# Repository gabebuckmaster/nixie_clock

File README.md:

# Nixie Tube Clock

A minimalist nixie tube clock design in a cnc-machined hardwood case using IN12B tubes.

All of the design files and detailed assembly/compilation instructions for the electronics, mechanical components, and firmware can be found in the respective subfolders: <a href=electronics>Electronics</a>, <a href=mechanical>Mechanical</a>, and <a href=firmware>Firmware</a>. 

This design has gone through several iterations, mostly to simplify the design and remove extraneous features that I thought would be a good idea but ultimately weren't. While nixie tubes are beautiful, they objectively have some significant shortcomings as a display technology: their viewing angle is extremely limited, and they can't be dimmed to arbitrarily low brightnesses - not to mention the difficulty in working with the high voltages needed to drive them. Over the course of the project, the goal converged to showing off the beauty of nixie tubes with the minimum possible set of features, and I'm happy with how the final result aligns with this goal.

I learned a lot about cnc machining, and am left with a great respect for the people who do this for a living. An incredible amount of effort (and skill among those who practice this professionally) goes into simply clamping the work piece in a way that allows the router/mill the necessary access. I also learned a lot about boost converter design, specifically core losses, the huge range of magnetic core materials, and why power electronics people often advise against designing boost converters that operate in DCM.

## License and Disclaimer
I built this clock because I wanted it to exist, and I’m distributing the documentation in the hopes that others find it interesting and/or educational. To this end, the files provided in this repository are licensed under the MIT license unless otherwise noted a given file.

This design is not FCC, CE, or UL certified, and thus it is probably not legal nor advisable to sell this design as a finished product in your jurisdiction. This project involves potentially dangerous power tools, potentially lethal voltages, and potential fire hazard due to housing electronics in a flammable material. **If you choose to recreate any work documented in this repository, you do so entirely at your own risk.**

## Final Assembly
The bill of materials for the final assembly is in <a href="final_assembly_bom.csv">Final Assembly BOM</a>.

### Pseudo-exploded view of the final assembly

### Video of final assembly
<p align="center">

</p>
Click through for longer/higher resolution video of final assembly.

## More Photos
### Final Assembly

### Electronics

### Clock Body

### Back Panel

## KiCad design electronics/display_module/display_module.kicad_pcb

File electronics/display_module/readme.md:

# Display Module

This PCB includes the nixie tubes themselves, current limiting resistors, and the high voltage shift register. 

For assembly, see the  <a href="display_module_bom.csv">BOM</a> and <a href="gerbers/display_module-F_Fab.pdf">fab drawing</a>

<a href="control_module.pdf">Schematic PDF</a>

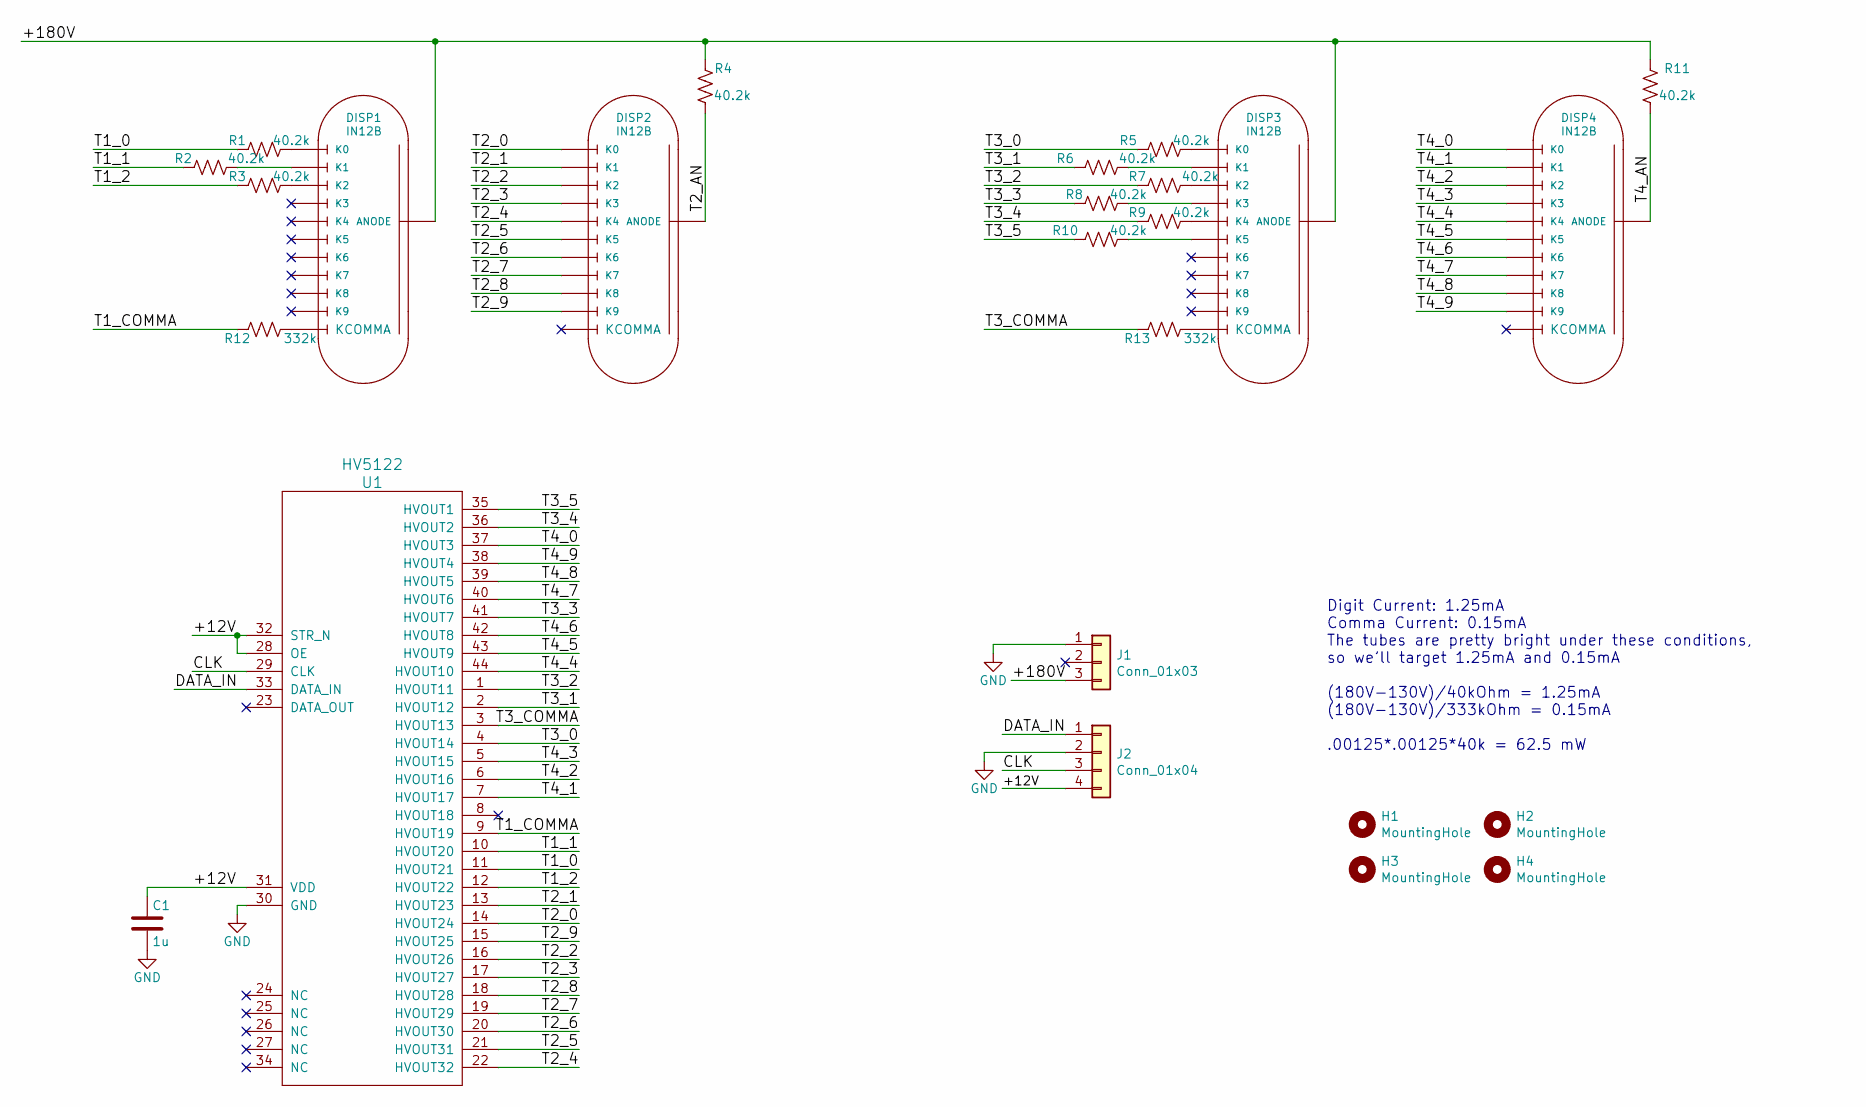
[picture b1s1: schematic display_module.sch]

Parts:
C1: 1u; C_0805_2012Metric
DISP1, DISP2, DISP3, DISP4: IN12B; IN-12B_nosocket
H1, H2, H3, H4: MountingHole; MountingHole_2.2mm_M2
J1: Conn_01x03; PinHeader_1x03_P2.54mm_Vertical
J2: Conn_01x04; PinHeader_1x04_P2.54mm_Vertical
R1, R2, R3, R4, R5, R6, R7, R8, R9, R10, R11: 40.2k; R_0805_2012Metric
R12, R13: 332k; R_0805_2012Metric
U1: HV5122; PQFP-44_10x10mm_Pitch0.8mm

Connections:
/+12V: C1.1, J2.4, U1.28 (OE), U1.31 (VDD), U1.32 (STR_N)
/+180V: DISP1.1 (ANODE), DISP3.1 (ANODE), J1.3, R4.1, R11.1
/CLK: J2.3, U1.29 (CLK)
/DATA_IN: J2.1, U1.33 (DATA_IN)
/T1_0: R1.2, U1.11 (HVOUT21)
/T1_1: R2.2, U1.10 (HVOUT20)
/T1_2: R3.2, U1.12 (HVOUT22)
/T1_COMMA: R12.2, U1.9 (HVOUT19)
/T2_0: DISP2.2 (K0), U1.14 (HVOUT24)
/T2_1: DISP2.11 (K1), U1.13 (HVOUT23)
/T2_2: DISP2.10 (K2), U1.16 (HVOUT26)
/T2_3: DISP2.9 (K3), U1.17 (HVOUT27)
/T2_4: DISP2.8 (K4), U1.22 (HVOUT32)
/T2_5: DISP2.7 (K5), U1.21 (HVOUT31)
/T2_6: DISP2.6 (K6), U1.20 (HVOUT30)
/T2_7: DISP2.5 (K7), U1.19 (HVOUT29)
/T2_8: DISP2.4 (K8), U1.18 (HVOUT28)
/T2_9: DISP2.3 (K9), U1.15 (HVOUT25)
/T2_AN: DISP2.1 (ANODE), R4.2
/T3_0: R5.2, U1.4 (HVOUT14)
/T3_1: R6.2, U1.2 (HVOUT12)
/T3_2: R7.2, U1.1 (HVOUT11)
/T3_3: R8.2, U1.41 (HVOUT7)
/T3_4: R9.2, U1.36 (HVOUT2)
/T3_5: R10.2, U1.35 (HVOUT1)
/T3_COMMA: R13.2, U1.3 (HVOUT13)
/T4_0: DISP4.2 (K0), U1.37 (HVOUT3)
/T4_1: DISP4.11 (K1), U1.7 (HVOUT17)
/T4_2: DISP4.10 (K2), U1.6 (HVOUT16)
/T4_3: DISP4.9 (K3), U1.5 (HVOUT15)
/T4_4: DISP4.8 (K4), U1.44 (HVOUT10)
/T4_5: DISP4.7 (K5), U1.43 (HVOUT9)
/T4_6: DISP4.6 (K6), U1.42 (HVOUT8)
/T4_7: DISP4.5 (K7), U1.40 (HVOUT6)
/T4_8: DISP4.4 (K8), U1.39 (HVOUT5)
/T4_9: DISP4.3 (K9), U1.38 (HVOUT4)
/T4_AN: DISP4.1 (ANODE), R11.2
GND: C1.2, J1.1, J2.2, U1.30 (GND)
unnamed: DISP1.2 (K0), R1.1
unnamed: DISP1.10 (K2), R3.1
unnamed: DISP1.11 (K1), R2.1
unnamed: DISP1.12 (KCOMMA), R12.1
unnamed: DISP3.2 (K0), R5.1
unnamed: DISP3.7 (K5), R10.1
unnamed: DISP3.8 (K4), R9.1
unnamed: DISP3.9 (K3), R8.1
unnamed: DISP3.10 (K2), R7.1
unnamed: DISP3.11 (K1), R6.1
unnamed: DISP3.12 (KCOMMA), R13.1

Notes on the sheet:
Digit Current: 1.25mA Comma Current: 0.15mA The tubes are pretty bright under these conditions, so we’ll target 1.25mA and 0.15mA (180V-130V)/40kOhm = 1.25mA (180V-130V)/333kOhm = 0.15mA .00125*.00125*40k = 62.5 mW

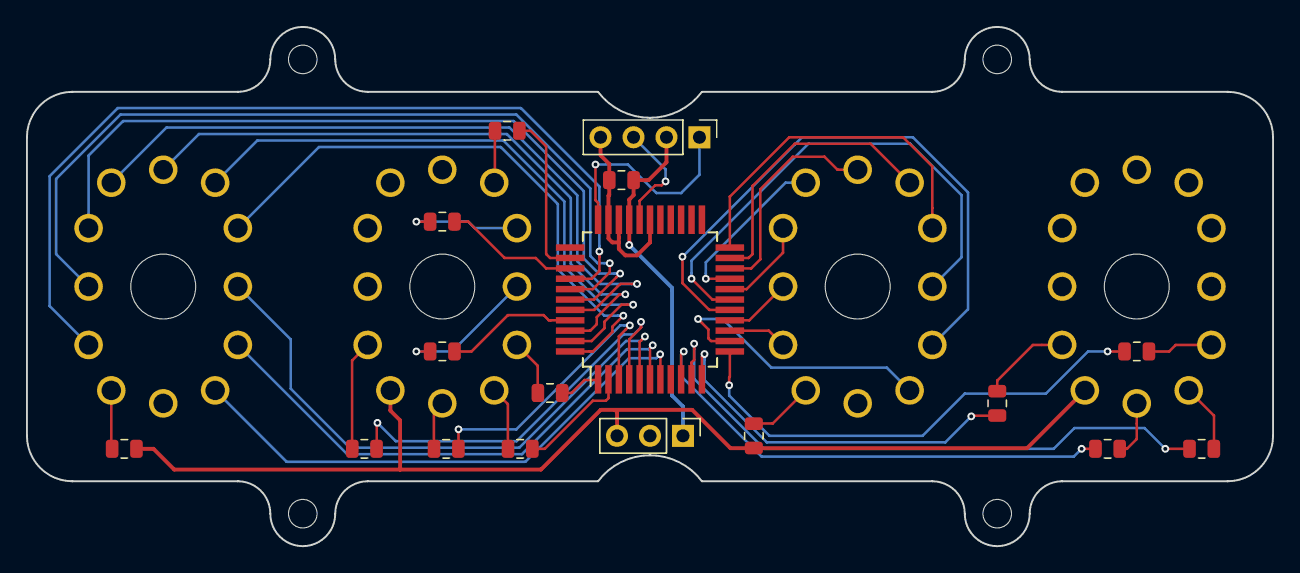
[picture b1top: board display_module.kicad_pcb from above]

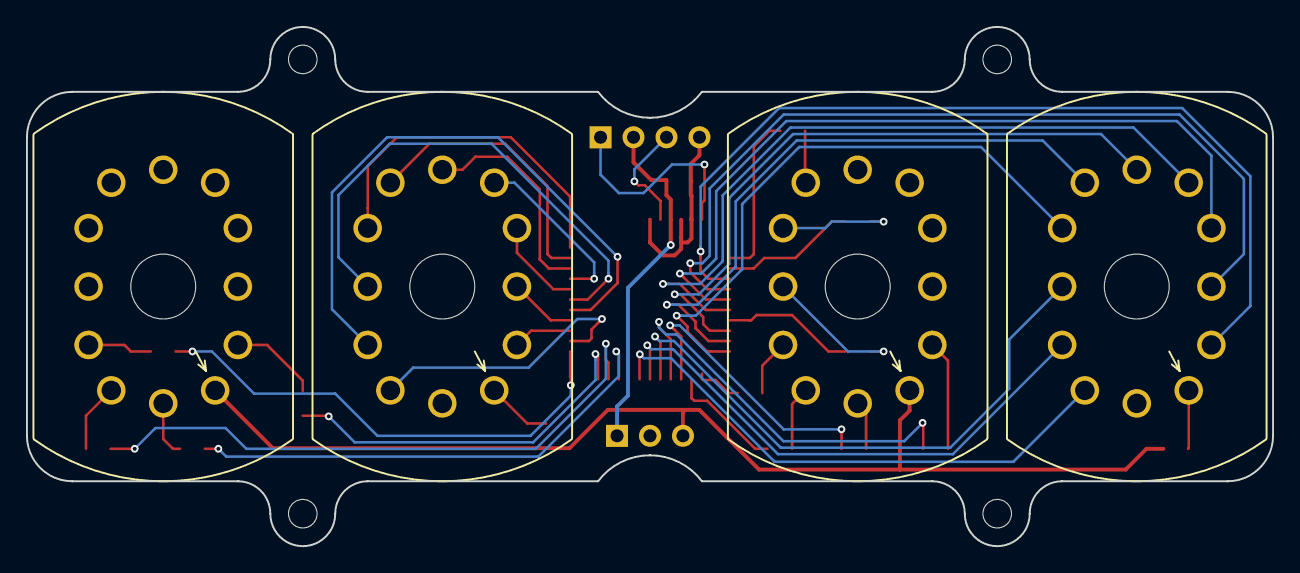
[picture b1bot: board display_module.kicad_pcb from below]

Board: 2 copper layers, 96.0 x 40.0 mm, 25 parts (4 on the bottom side), 49 nets.

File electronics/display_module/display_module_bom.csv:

Reference(s),Qty,Description,Value,Manufacturer,MPN
C1,1,1 uF Ceramic Capacitor X5R 25V 0805,1u,Generic,
"DISP1, DISP2, DISP3, DISP4",4,IN12B Nixie Tube,,,
J1,1,"0.1"" Male Pin Header 1x3 TH",,Generic,
J2,1,"0.1"" Male Pin Header 1x4 TH",,Generic,
"R1, R2, R3, R4, R5, R6, R7, R8, R9, R10, R11",11,1% Resistor 0805,40.2k,,
"R12, R13",2,1% Resistor 0805,332k,,
U1,1,High Voltage Shift Register,,Microchip,HV5122

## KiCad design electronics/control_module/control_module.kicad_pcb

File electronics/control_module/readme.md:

# Control Module

This PCB includes the microcontroller, a temperature compensated real time clock IC with battery backup, and the boost converter that generates the 180V supply for the nixie tubes.

For assembly, see the  <a href="control_module_bom.csv">BOM</a> and <a href="gerbers/control_module-F_Fab.pdf">fab drawing</a>

<a href="control_module.pdf">Schematic PDF</a>

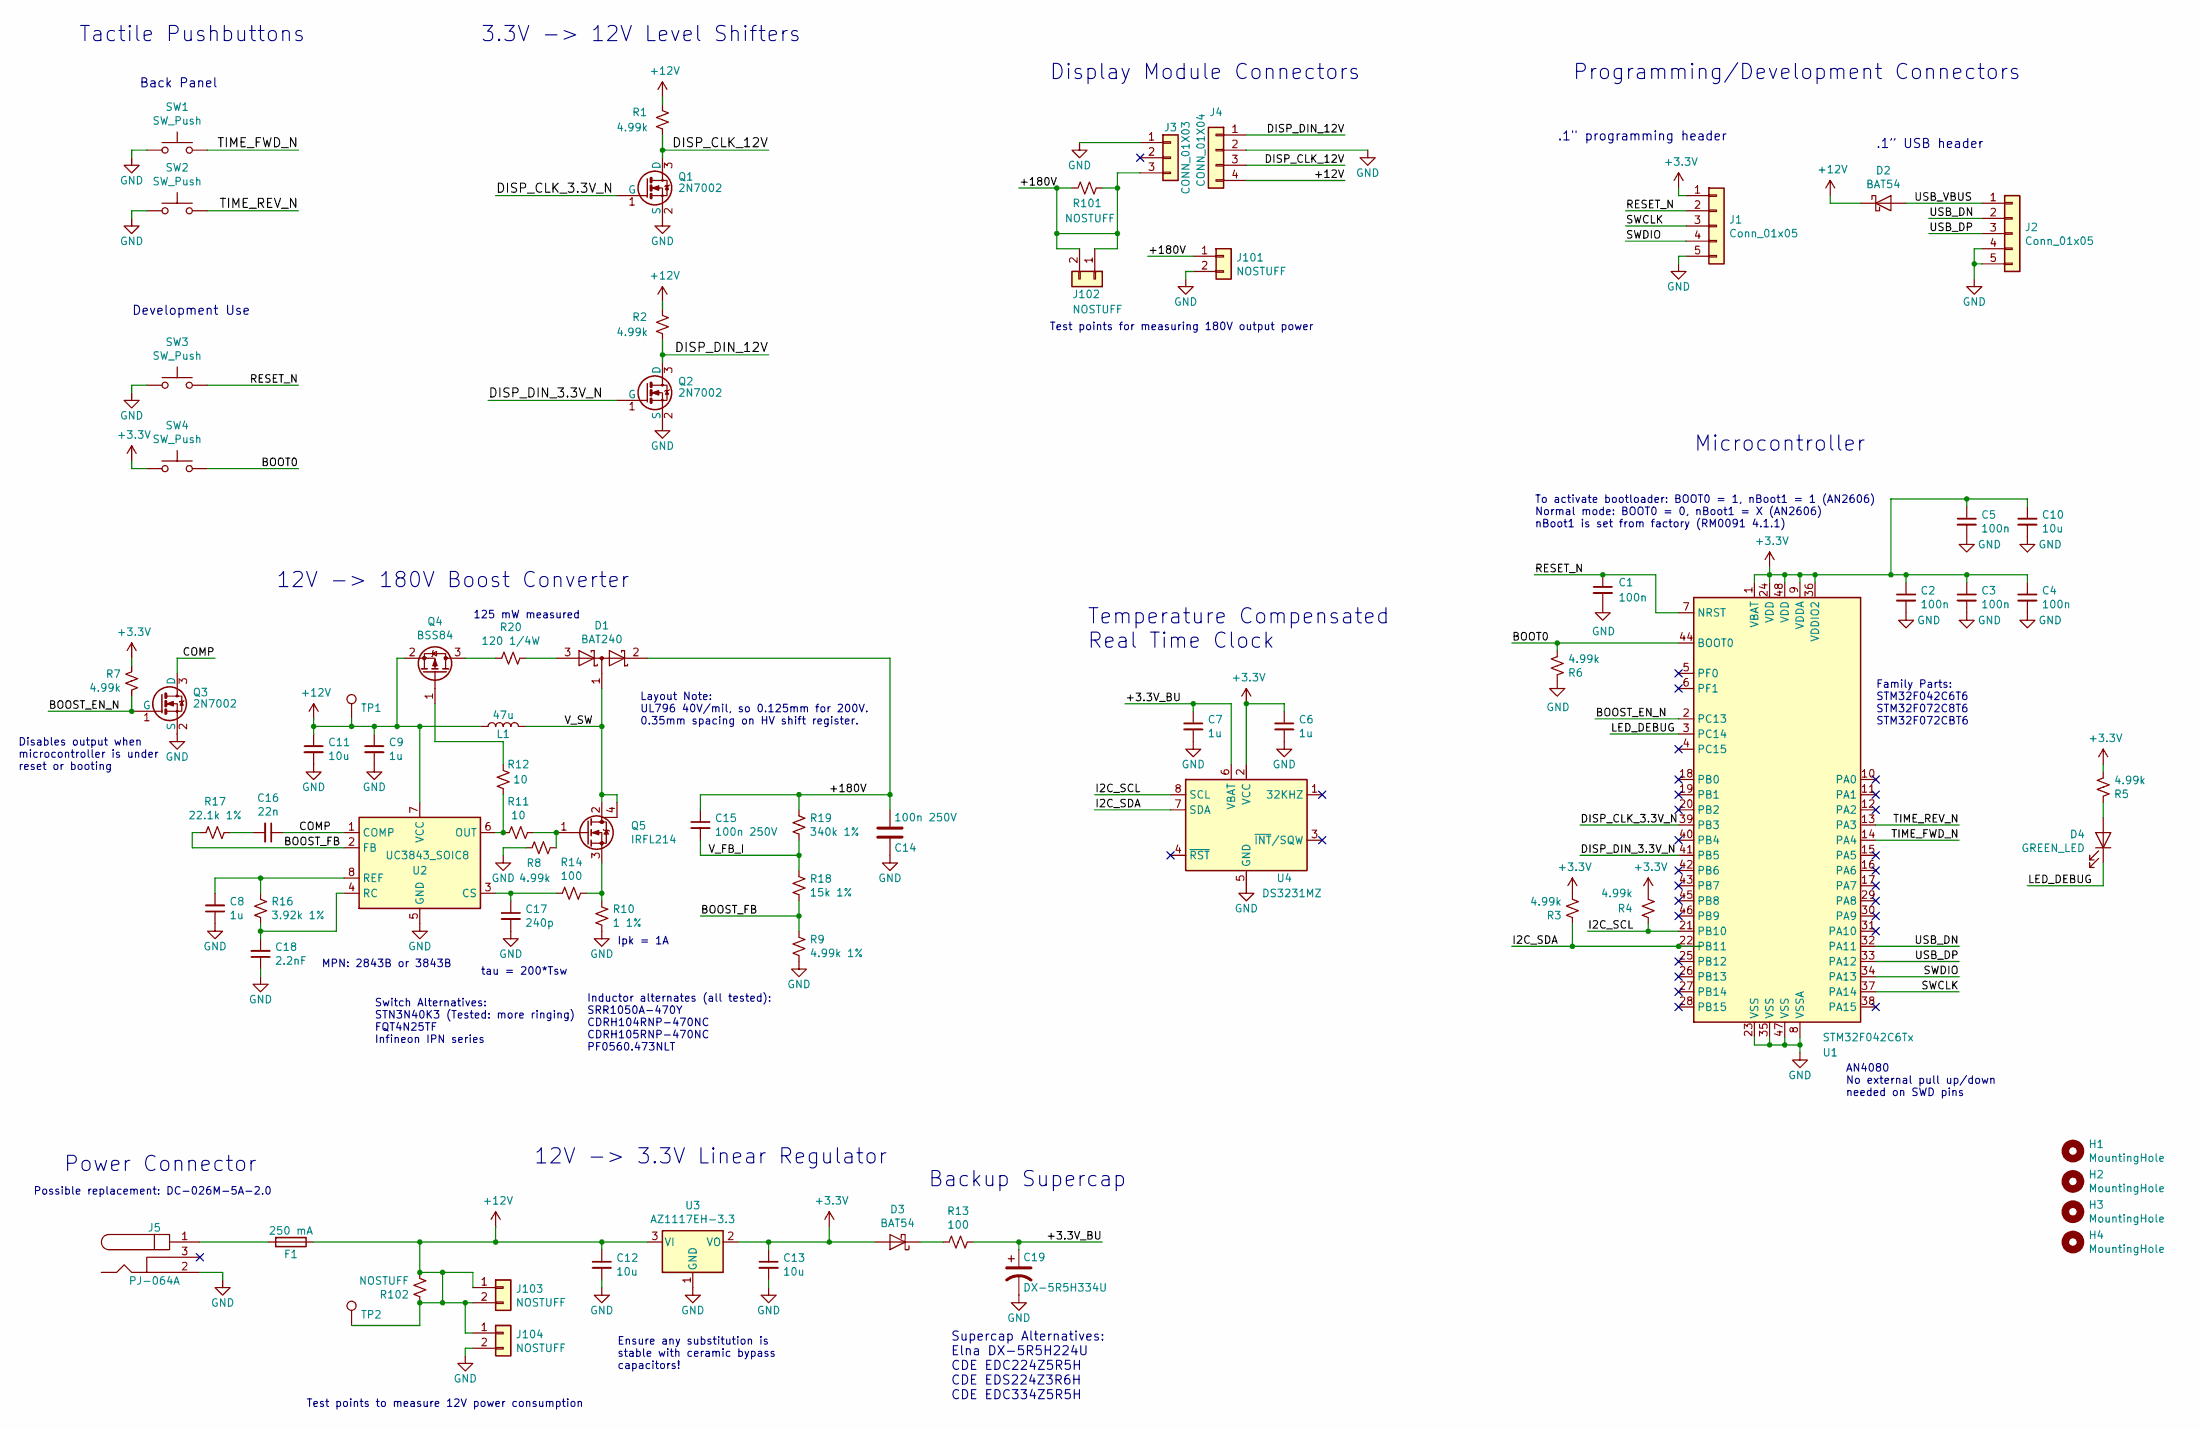
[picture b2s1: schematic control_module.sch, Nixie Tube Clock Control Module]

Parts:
C1, C2, C3, C4, C5: 100n; C_0805_2012Metric
C6, C7, C8, C9: 1u; C_0805_2012Metric
C10, C11, C12, C13: 10u; C_0805_2012Metric
C14, C15: 100n 250V; C_1206_3216Metric
C16: 22n; C_0805_2012Metric
C17: 240p; C_0805_2012Metric
C18: 2.2nF; C_0805_2012Metric
C19: DX-5R5H334U; EEC-S0HD334H
D1: BAT240; SOT-23
D2, D3: BAT54; D_SOD-123
D4: GREEN_LED; LED_0805_2012Metric
F1: 250 mA; Fuse_1206_3216Metric_Pad1.42x1.75mm_HandSolder
H1, H2, H3, H4: MountingHole; MountingHole_2.2mm_M2
J1, J2: Conn_01x05; PinHeader_1x05_P2.54mm_Vertical_NoSilk
J3: CONN_01X03; PinHeader_1x03_P2.54mm_Vertical
J4: CONN_01X04; PinHeader_1x04_P2.54mm_Vertical
J5: PJ-064A; PJ-064X
J101, J102, J103, J104: NOSTUFF; PinHeader_1x02_P2.54mm_Vertical
L1: 47u; L_TDK_SLF10145; Part Number 74404064221
Q1, Q2, Q3: 2N7002; SOT-23
Q4: BSS84; SOT-23
Q5: IRFL214; SOT-223
R1, R2, R3, R4, R5, R6, R7, R8: 4.99k; R_0805_2012Metric
R9: 4.99k 1%; R_0805_2012Metric
R10: 1 1%; R_0805_2012Metric
R11, R12: 10; R_0805_2012Metric
R13, R14: 100; R_0805_2012Metric
R16: 3.92k 1%; R_0805_2012Metric
R17: 22.1k 1%; R_0805_2012Metric
R18: 15k 1%; R_1206_3216Metric
R19: 340k 1%; R_1206_3216Metric
R20: 120 1/4W; R_1206_3216Metric
R101, R102: NOSTUFF; R_0805_2012Metric
SW1, SW2: SW_Push; SW_PUSH_6mm_H4.3mm
SW3, SW4: SW_Push; SW_SPST_TL3342
TP1, TP2: TestPoint; TestPoint_Pad_D1.0mm
U1: STM32F042C6Tx; LQFP-48_7x7mm_P0.5mm
U2: UC3843_SOIC8; SOIC-8_3.9x4.9mm_P1.27mm
U3: AZ1117EH-3.3; SOT-223-3_TabPin2
U4: DS3231MZ; SOIC-8_3.9x4.9mm_P1.27mm

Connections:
+3V3: C2.1, C3.1, C4.1, C5.1, C6.1, C10.1, C13.1, D3.2 (A), J1.1, R3.2, R4.2, R5.2, R7.1, SW4.1, U1.1 (VBAT), U1.9 (VDDA), U1.24 (VDD), U1.36 (VDDIO2), U1.48 (VDD), U3.2 (VO), U4.2 (VCC)
+12V: C9.1, C11.1, C12.1, D2.1 (K), F1.1, J4.4, J103.1, J103.2, J104.1, L1.1, Q4.2 (S), R1.2, R2.2, R102.1, R102.2, TP1.1, TP2.1, U2.7 (VCC), U3.3 (VI)
/+3.3V_BU: C7.1, C19.1, R13.1, U4.6 (VBAT)
/+180V: C14.2, C15.1, D1.2 (K), J3.3, J101.1, J102.1, J102.2, R19.1, R101.1, R101.2
/BOOST_EN_N: Q3.1 (G), R7.2, U1.2 (PC13)
/BOOST_FB: R9.1, R17.2, R18.2, U2.2 (FB)
/BOOT0: R6.2, SW4.2, U1.44 (BOOT0)
/COMP: C16.1, Q3.3 (D), U2.1 (COMP)
/DISP_CLK_3.3V_N: Q1.1 (G), U1.39 (PB3)
/DISP_CLK_12V: J4.3, Q1.3 (D), R1.1
/DISP_DIN_3.3V_N: Q2.1 (G), U1.41 (PB5)
/DISP_DIN_12V: J4.1, Q2.3 (D), R2.1
/I2C_SCL: R4.1, U1.21 (PB10), U4.8 (SCL)
/I2C_SDA: R3.1, U1.22 (PB11), U4.7 (SDA)
/LED_DEBUG: D4.1 (K), U1.3 (PC14)
/RESET_N: C1.1, J1.2, SW3.2, U1.7 (NRST)
/SWCLK: J1.3, U1.37 (PA14)
/SWDIO: J1.4, U1.34 (PA13)
/TIME_FWD_N: SW1.2, U1.14 (PA4)
/TIME_REV_N: SW2.2, U1.13 (PA3)
/USB_DN: J2.2, U1.32 (PA11)
/USB_DP: J2.3, U1.33 (PA12)
/USB_VBUS: D2.2 (A), J2.1
/V_FB_I: C15.2, R18.1, R19.2
/V_SW: D1.1 (common), L1.2, Q5.2 (D), Q5.4 (D)
GND: C1.2, C2.2, C3.2, C4.2, C5.2, C6.2, C7.2, C8.1, C9.2, C10.2, C11.2, C12.2, C13.2, C14.1, C17.2, C18.1, C19.2, J1.5, J2.4, J2.5, J3.1, J4.2, J5.2, J101.2, J104.2, Q1.2 (S), Q2.2 (S), Q3.2 (S), R6.1, R8.2, R9.2, R10.2, SW1.1, SW2.1, SW3.1, U1.8 (VSSA), U1.23 (VSS), U1.35 (VSS), U1.47 (VSS), U2.5 (GND), U3.1 (GND), U4.5 (GND)
unnamed: C8.2, R16.2, U2.8 (REF)
unnamed: C16.2, R17.1
unnamed: C17.1, R14.2, U2.3 (CS)
unnamed: C18.2, R16.1, U2.4 (RC)
unnamed: D1.3 (A), R20.1
unnamed: D3.1 (K), R13.2
unnamed: D4.2 (A), R5.1
unnamed: F1.2, J5.1
unnamed: Q4.1 (G), R12.2
unnamed: Q4.3 (D), R20.2
unnamed: Q5.1 (G), R8.1, R11.1
unnamed: Q5.3 (S), R10.1, R14.1
unnamed: R11.2, R12.1, U2.6 (OUT)

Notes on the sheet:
Supercap Alternatives: Elna DX-5R5H224U CDE EDC224Z5R5H CDE EDS224Z3R6H CDE EDC334Z5R5H
Display Module Connectors
Back Panel
.1" programming header
Layout Note: UL796 40V/mil, so 0.125mm for 200V. 0.35mm spacing on HV shift register.
tau = 200*Tsw
Ipk = 1A
Possible replacement: DC-026M-5A-2.0
Switch Alternatives: STN3N40K3 (Tested: more ringing) FQT4N25TF Infineon IPN series
.1” USB header
To activate bootloader: BOOT0 = 1, nBoot1 = 1 (AN2606) Normal mode: BOOT0 = 0, nBoot1 = X (AN2606) nBoot1 is set from factory (RM0091 4.1.1)
AN4080 No external pull up/down needed on SWD pins
125 mW measured
Ensure any substitution is stable with ceramic bypass capacitors!
MPN: 2843B or 3843B
Family Parts: STM32F042C6T6 STM32F072C8T6 STM32F072CBT6
Development Use
Test points for measuring 180V output power
Test points to measure 12V power consumption
12V -> 180V Boost Converter
12V -> 3.3V Linear Regulator
3.3V -> 12V Level Shifters
Tactile Pushbuttons
Temperature Compensated Real Time Clock
Backup Supercap
Programming/Development Connectors
Microcontroller
Disables output when microcontroller is under reset or booting
Power Connector
Inductor alternates (all tested): SRR1050A-470Y CDRH104RNP-470NC CDRH105RNP-470NC PF0560.473NLT

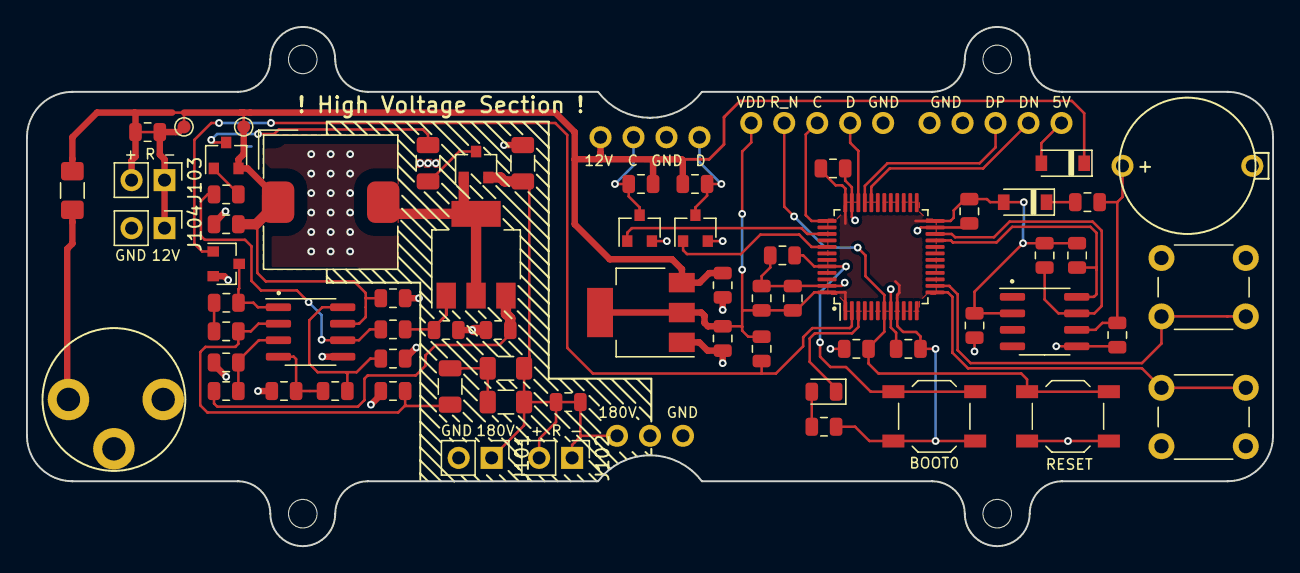
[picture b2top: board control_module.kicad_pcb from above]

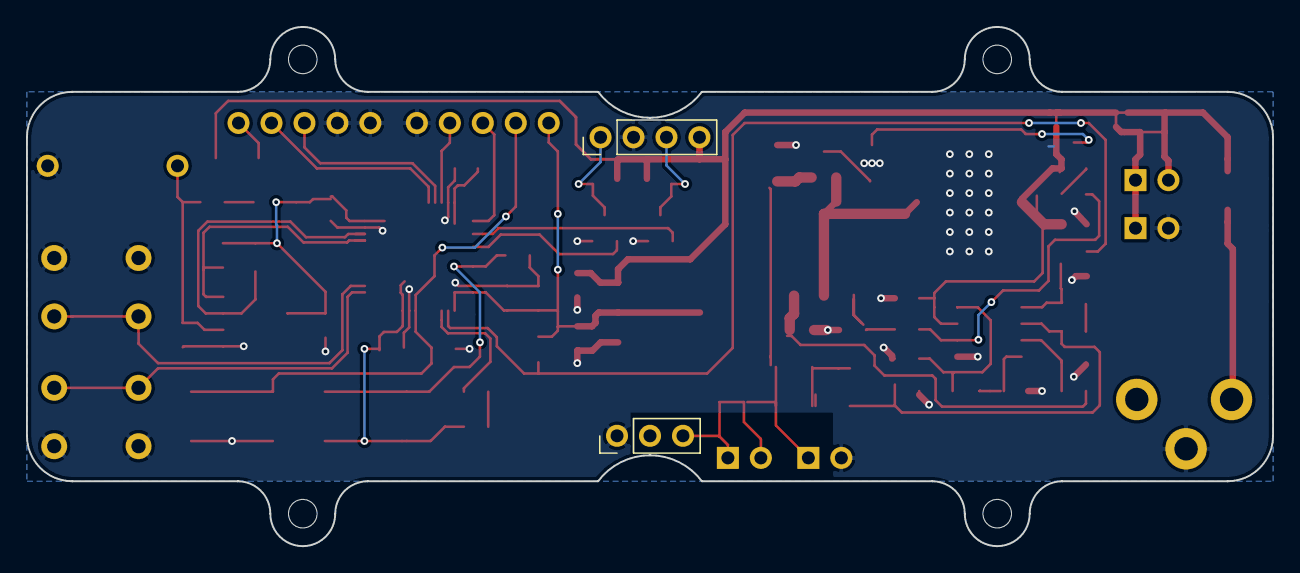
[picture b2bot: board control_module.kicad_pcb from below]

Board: 2 copper layers, 96.0 x 40.0 mm, 74 parts (2 on the bottom side), 39 nets.

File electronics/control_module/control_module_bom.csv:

Reference(s),Qty,Description,Value,Manufacturer,MPN,Notes
"C1, C2, C3, C4, C5",5,100 nF Ceramic Capacitor X5R 25V 0805,100n,Generic,,
"C6, C7, C8, C9",4,1 uF Ceramic Capacitor X5R 25V 0805,1u,Generic,,
"C10, C11, C12, C13",4,10uF Ceramic Capacitor X5R 25V 0805,10u,Generic,,
"C14, C15",2,100 nF Ceramic Capacitor 250V 1206,100n 250V,Generic,,
C16,1,22 nF Ceramic Capacitor 25V 0805,22n ,Generic,,
C17,1,240 pF Ceramic Capacitor 25V 0805,240p,Generic,,
C18,1,2.2 nF Ceramic Capacitor 25V 0805,2.2nF,Generic,,
C19,1,330 mF Supercapacitor 5.5V 10mm Dia.,330mF,Elna,DX-5R5H334U,
D1,1,Schottky Diode (Dual) 400 mA 240V SOT23,,Infineon,BAT240AE6327HTSA1,
"D2, D3",2,Schottky Diode 200 mA 30V SOD123,,ON Semiconductor,BAT54T1G,
D4,1,Green LED 0805,,Generic,,
F1,1,250 mA Surface Mount Fuse 1206,250 mA,Generic,,
"J1, J2",2,"0.1"" Header Footprint",NO STUFF (programming ports),,,
J3,1,"0.1"" Female Header 1x3 TH",,Generic,,
J4,1,"0.1"" Female Header 1x4 TH",,Generic,,
J5,1,"Barrel Jack, 2mmx5.5mm TH",,CUI,PJ-064A,
"J101, J102, J103, J104",4,"0.1"" Header Footprint",NO STUFF (efficiency measurement),,,
L1,1,47uH Inductor 2.3A 10.5mm x 10.3mm SMD,47u,Sumida,CDRH105RNP-470NC,
"Q1, Q2, Q3",3,N MOSFET 60V 115 mA SOT23,2N7002,Generic,,
Q4,1,P MOSFET 50V 130 mA SOT23,BSS84,Generic,,
Q5,1,N MOSFET 250V 790 mA SOT223,IRFL214,Vishay Siliconix,IRFL214TRPBF,
"R1, R2, R3, R4, R5, R6, R7, R8",8,Resistor 1% 0805,4.99k,Generic,,
R9,1,Resistor 1% 0805,4.99k 1%,Generic,,
R10,1,Resistor 1% 0805,1 1%,Generic,,
"R11, R12",2,Resistor 1% 0805,10,Generic,,
"R13, R14",2,Resistor 1% 0805,100,Generic,,
R16,1,Resistor 1% 0805,3.92k 1%,Generic,,
R17,1,Resistor 1% 0805,22.1k 1%,Generic,,
R18,1,Resistor 1% 1206,15k 1%,Generic,,
R19,1,Resistor 1% 1206,340k 1%,Generic,,
R20,1,Resistor 5% 1206,120 1/4W,Generic,,
"R101, R102",2,Resistor 0805,NO STUFF (efficiency measurement),,,
"SW1, SW2",2,Tactile Pushbutton 6mmx6mmx15mm TH,,Generic,,
"SW3, SW4",2,Tactile Pushbutton 5.2mmx5.2mm SMD,,Generic,Ex: Shou Han TS5215A,
U1,1,Microcontroller QFP-48,,STMicroelectronics,STM32F042C6T6,
U2,1,Switching Regualtor Controller SOIC-8,,ON Semiconductor,UC3843BD1G,
U3,1,3.3V LDO SOT223,,Diodes Inc,AZ1117EH-3.3,
U4,1,Real Time Clock/TCXO SOIC-8,,Maxim Integrated,DS3231MZ,DS3232MZ should be a functional equivalent (unverified)

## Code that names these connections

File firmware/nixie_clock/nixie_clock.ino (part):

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uint32_t time_rev_last_state = 0;

// Signal assignments from control PCB
#define DISPLAY_CLOCK_N PB3
#define DISPLAY_DATA_N PB5
#define SPI_MISO_DUMMY PB4
#define BOOST_EN_N PC13
#define LED_DEBUG_N PC14
#define TIME_FWD_N PA4
#define TIME_REV_N PA3
#define I2C_SDA PB11
#define I2C_SCL PB10

// Signal Assignments from display PCB
const uint8_t tube1[] = {31-20, 31-19, 31-21};
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
  // Initialize GPIOs
  digitalWrite(BOOST_EN_N, HIGH);
  pinMode(BOOST_EN_N, OUTPUT);
  
  digitalWrite(DISPLAY_CLOCK_N, HIGH);
  digitalWrite(DISPLAY_DATA_N, HIGH);
  pinMode(DISPLAY_CLOCK_N, OUTPUT);
  pinMode(DISPLAY_DATA_N, OUTPUT);

  pinMode(TIME_FWD_N, INPUT_PULLUP);
  pinMode(TIME_REV_N, INPUT_PULLUP);

  digitalWrite(LED_DEBUG_N, HIGH);
  pinMode(LED_DEBUG_N, OUTPUT);
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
